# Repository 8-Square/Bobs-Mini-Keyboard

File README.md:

# Bobs Mini Keyboard

My first mini keyboard project.
The mini keyboard contains 10 keys and 3 simple leds

## Specifications

### PCB

The PCB's overall size is 110 x 80

**Images Of the PCB:**
|Schematic |PCB |
|--------------|--------|
|  | 

### CAD

The CAD casing size is 130 x 100 x 14.5

**Overall Casing**

I used Fusion for the casing of the PCB

### Firmware

I used KMK (python) for the mini keyboards firmware

## BOM

- 1x XIAO RP2040
- 10x SW Cherry MX Switches
- 3x SK6812Mini-E

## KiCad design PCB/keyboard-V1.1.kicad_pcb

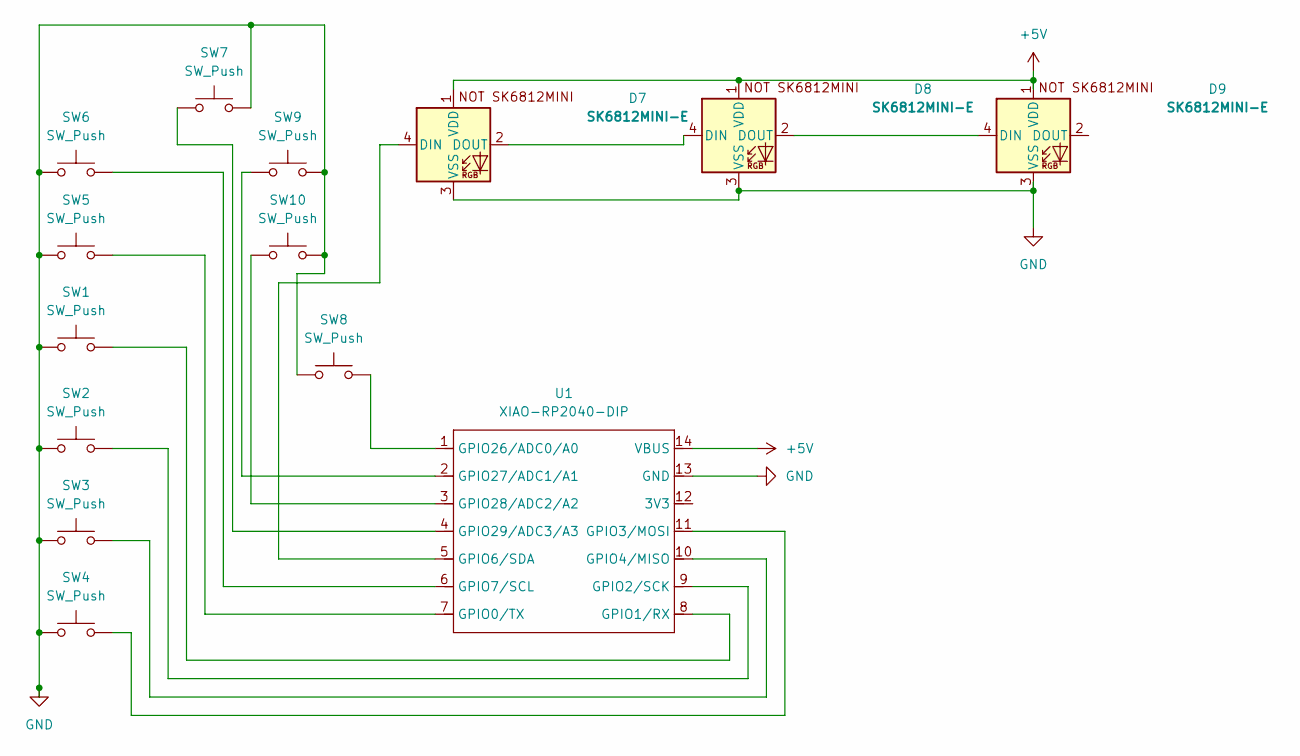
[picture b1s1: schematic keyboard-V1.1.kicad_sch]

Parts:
D7, D8, D9: SK6812MINI-E; LED_SK6812MINI_PLCC4_3.5x3.5mm_P1.75mm
SW1, SW2, SW3, SW4, SW5, SW6, SW7, SW8, SW9, SW10: SW_Push; SW_Cherry_MX_1.00u_PCB
U1: XIAO-RP2040-DIP

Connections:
+5V: D7.1 (VDD), D8.1 (VDD), D9.1 (VDD), U1.14 (VBUS)
GND: D7.3 (VSS), D8.3 (VSS), D9.3 (VSS), SW1.1, SW2.1, SW3.1, SW4.1, SW5.1, SW6.1, SW7.2, SW8.1, SW9.2, SW10.2, U1.13 (GND)
unnamed: D7.4 (DIN), U1.5 (GPIO6/SDA)
unnamed: D7.2 (DOUT), D8.4 (DIN)
unnamed: D8.2 (DOUT), D9.4 (DIN)
unnamed: SW5.2, U1.7 (GPIO0/TX)
unnamed: SW1.2, U1.8 (GPIO1/RX)
unnamed: SW2.2, U1.9 (GPIO2/SCK)
unnamed: SW4.2, U1.11 (GPIO3/MOSI)
unnamed: SW3.2, U1.10 (GPIO4/MISO)
unnamed: SW6.2, U1.6 (GPIO7/SCL)
unnamed: SW8.2, U1.1 (GPIO26/ADC0/A0)
unnamed: SW9.1, U1.2 (GPIO27/ADC1/A1)
unnamed: SW10.1, U1.3 (GPIO28/ADC2/A2)
unnamed: SW7.1, U1.4 (GPIO29/ADC3/A3)

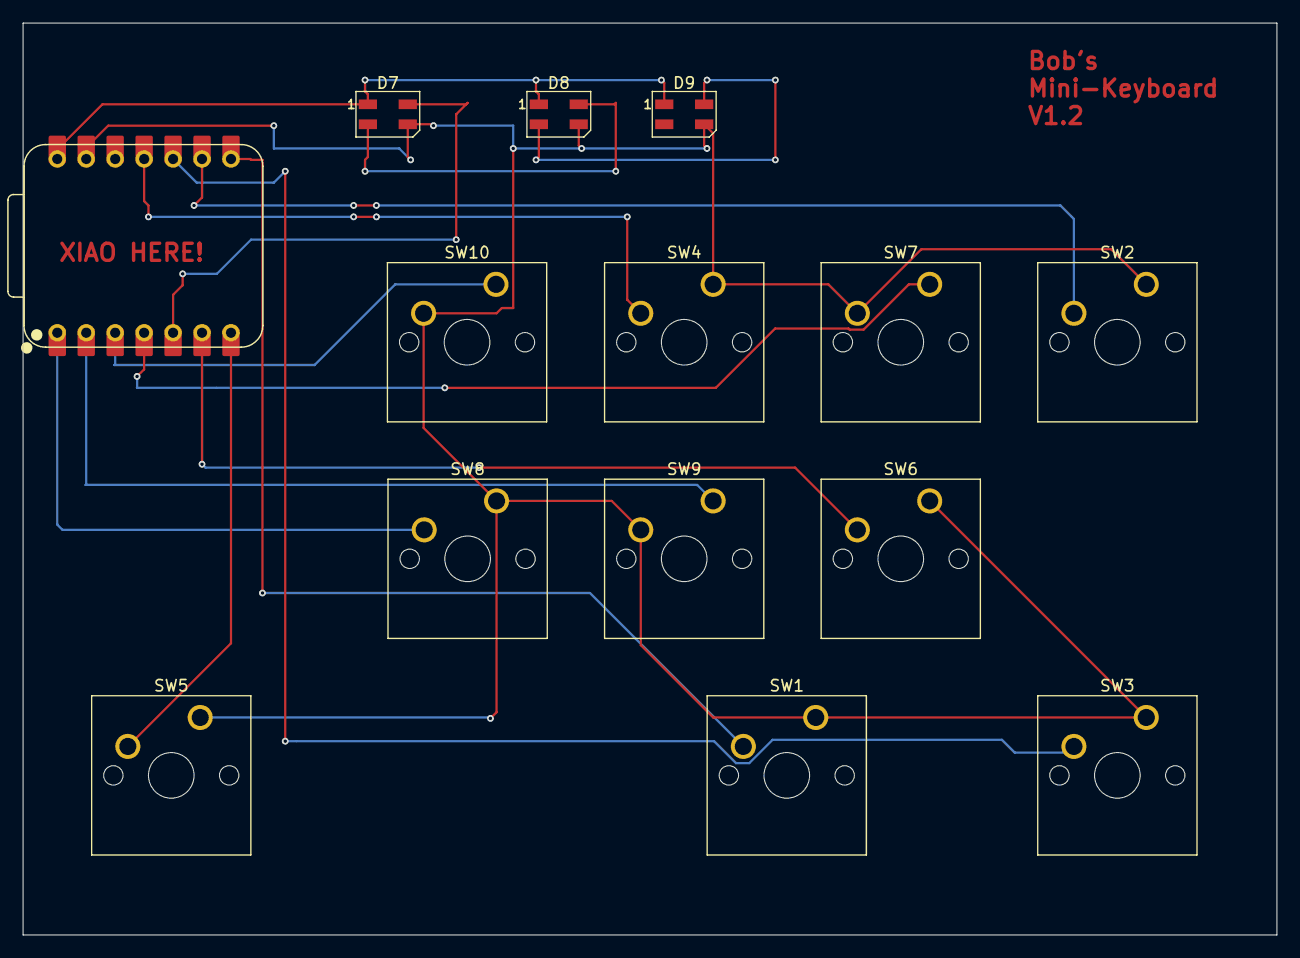
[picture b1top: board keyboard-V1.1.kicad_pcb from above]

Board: 2 copper layers, 110.0 x 80.0 mm, 14 parts (0 on the bottom side), 15 nets.

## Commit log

2025-12-21 Keyboard Files
2025-12-21 tried to update the skmini thing
    itssssss noooooooot workingggggggggggg
2025-12-26 V1.2
    Changes to Fusion Models + Readme
2025-12-26 Readme Changes
2025-12-27 Added .stl
2025-12-27 README changes again
2025-12-28 Complete keyboard stl
